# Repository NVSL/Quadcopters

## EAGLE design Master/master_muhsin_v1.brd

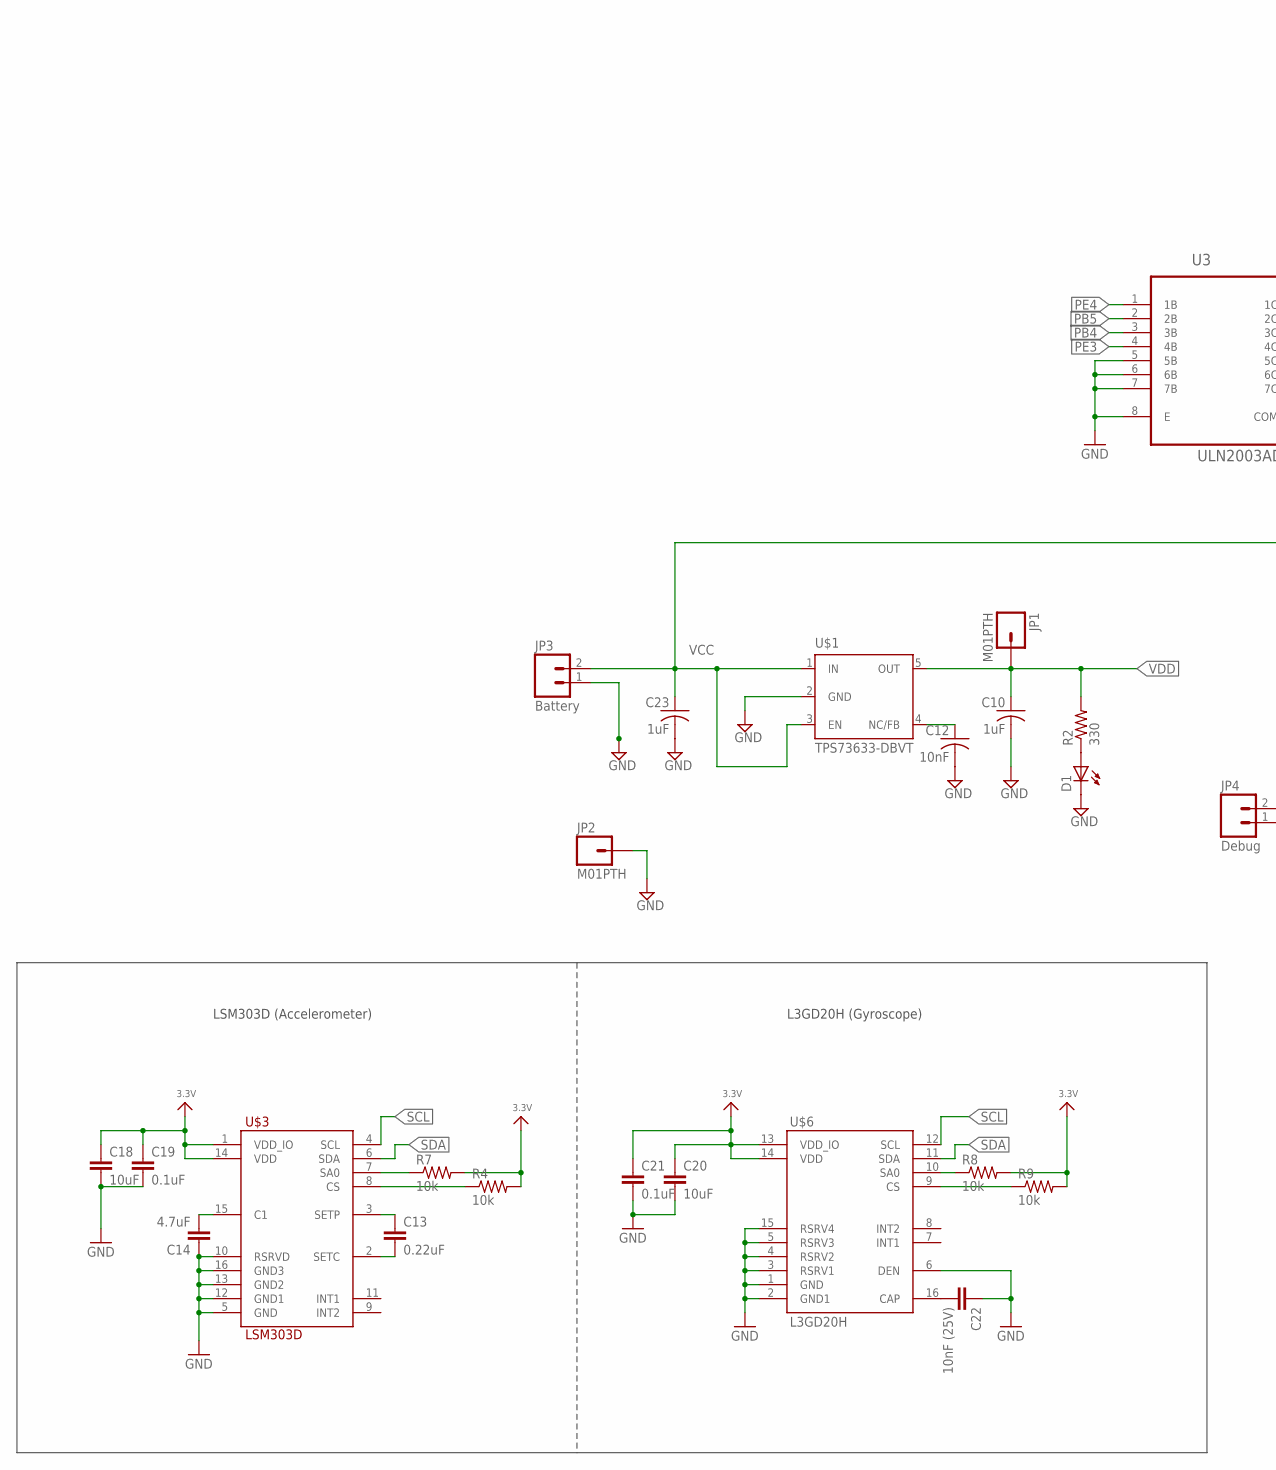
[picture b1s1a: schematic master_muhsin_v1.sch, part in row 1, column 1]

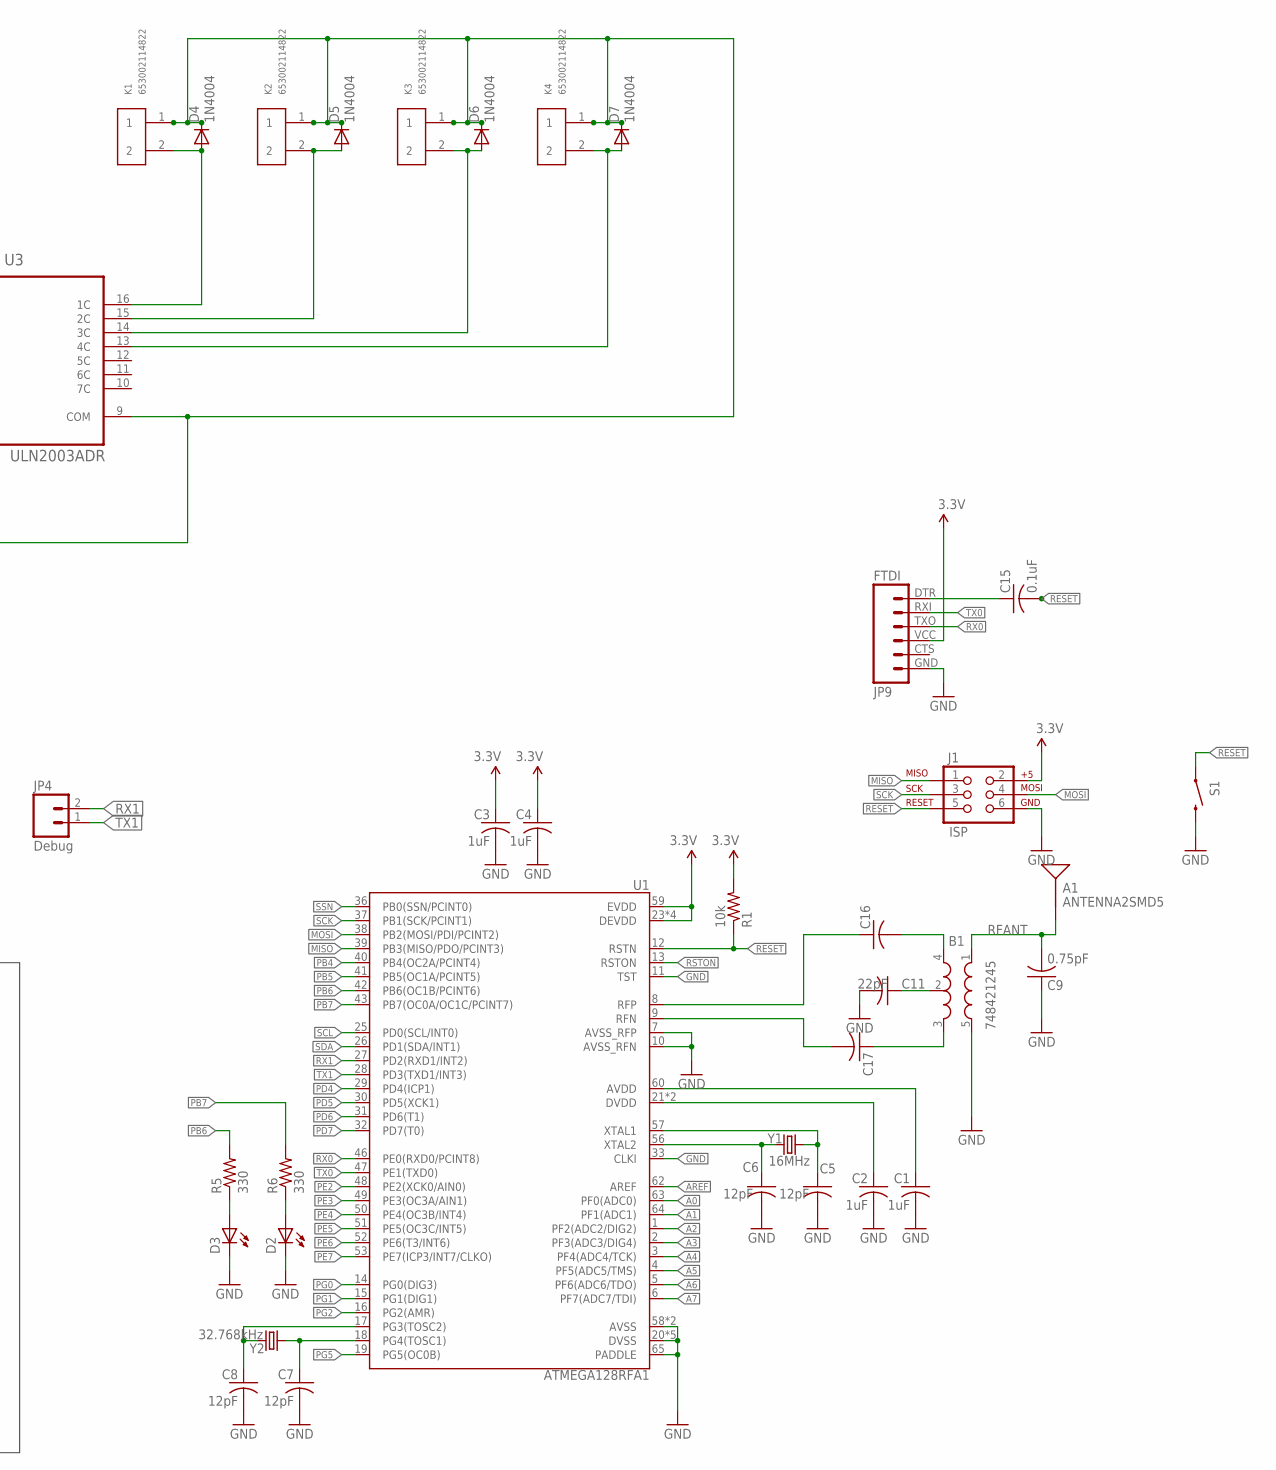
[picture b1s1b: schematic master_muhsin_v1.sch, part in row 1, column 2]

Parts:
A1: ANTENNA2SMD5; ANTENNA-CHIP5
B1: 748421245; BALUN
C1, C2, C3, C4, C10, C23: 1uF; C0805
C5, C6, C7, C8: 12pF; C0805
C9: 0.75pF; C0805
C11: 22pF; C0805
C12: 10nF; C0805
C13: 0.22uF; 0805
C14: 4.7uF; 0805
C15: 0.1uF; C0805
C16, C17: C-USC0805; C0805
C18, C20: 10uF; 0805
C19, C21: 0.1uF; 0805
C22: 10nF (25V); 0805
D1, D2, D3: LED5MM
D4, D5, D6, D7: 1N4004; DO41-10; MPN 1N4004
J1: ISP; 2X3-NS
JP1, JP2: M01PTH; 1X01
JP3: Battery; 1X02
JP4: Debug; 1X02
JP9: FTDI; FTDI_BASIC
K1, K2, K3, K4: 653002114822
R1: 10k; R0805
R2, R5, R6: 330; R0805
R4, R7, R8, R9: 10k; 0805
S1: SWITCH-MOMENTARY-2SMD; TACTILE_SWITCH_SMD
U1: ATMEGA128RFA1; QFN-64
U3: ULN2003ADR; SOIC127P600X175-16N
U$1: TPS73633-DBVT; SOT23-DBV
U$3: LSM303D; LGA16_3X3MM
U$6: L3GD20H; LGA16_3X3MM
Y1: 16MHz; CRYSTAL-SMD-5X3
Y2: 32.768kHz; CRYSTAL-32KHZ-SMD

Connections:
3.3V: C3.1, C4.1, C18.1, C19.1, C20.1, C21.1, J1.2, JP9.VCC (4), R1.2, R4.2, R7.2, R8.2, R9.2, U1.23 (DEVDD), U1.34 (DEVDD), U1.44 (DEVDD), U1.54 (DEVDD), U1.59 (EVDD), U$3.1 (VDD_IO), U$3.14 (VDD), U$6.13 (VDD_IO), U$6.14 (VDD)
A0: U1.63 (PF0(ADC0))
A1: U1.64 (PF1(ADC1))
A2: U1.1 (PF2(ADC2/DIG2))
A3: U1.2 (PF3(ADC3/DIG4))
A4: U1.3 (PF4(ADC4/TCK))
A5: U1.4 (PF5(ADC5/TMS))
A6: U1.5 (PF6(ADC6/TDO))
A7: U1.6 (PF7(ADC7/TDI))
AREF: U1.62 (AREF)
AVDD: C1.1, U1.60 (AVDD)
DTR: C15.1, JP9.DTR (1)
DVDD: C2.1, U1.21 (DVDD), U1.22 (DVDD)
GND: B1.5 (GND), C1.2, C2.2, C3.2, C4.2, C5.2, C6.2, C7.2, C8.2, C9.1, C10.2, C11.2, C12.2, C14.1, C18.2, C19.2, C20.2, C21.2, C22.1, C23.2, D1.K (C), D2.K (C), D3.K (C), J1.6, JP2.1, JP3.1, JP9.GND (6), S1.3 (2), U1.7 (AVSS_RFP), U1.10 (AVSS_RFN), U1.11 (TST), U1.20 (DVSS), U1.24 (DVSS), U1.33 (CLKI), U1.35 (DVSS), U1.45 (DVSS), U1.55 (DVSS), U1.58 (AVSS), U1.61 (AVSS), U1.65 (PADDLE), U3.5 (5B), U3.6 (6B), U3.7 (7B), U3.8 (E), U$1.2 (GND), U$3.5 (GND), U$3.10 (RSRVD), U$3.12 (GND1), U$3.13 (GND2), U$3.16 (GND3), U$6.1 (GND), U$6.2 (GND1), U$6.3 (RSRV1), U$6.4 (RSRV2), U$6.5 (RSRV3), U$6.6 (DEN), U$6.15 (RSRV4)
MISO: J1.1, U1.39 (PB3(MISO/PDO/PCINT3))
MOSI: J1.4, U1.38 (PB2(MOSI/PDI/PCINT2))
unnamed: C12.1, U$1.4 (NC/FB)
unnamed: D1.A, R2.1
unnamed: C5.1, U1.57 (XTAL1), Y1.3 (2)
unnamed: C6.1, U1.56 (XTAL2), Y1.1
unnamed: C7.1, U1.18 (PG4(TOSC1)), Y2.X1 (1)
unnamed: C8.1, U1.17 (PG3(TOSC2)), Y2.X2 (2)
unnamed: B1.2 (GND), C11.1
unnamed: D3.A, R5.1
unnamed: C13.1, U$3.3 (SETP)
unnamed: B1.4 (OUT1), C16.2
unnamed: B1.3 (OUT2), C17.1
unnamed: C13.2, U$3.2 (SETC)
unnamed: D2.A, R6.1
unnamed: R4.1, U$3.8 (CS)
unnamed: R7.1, U$3.7 (SA0)
unnamed: C14.2, U$3.15 (C1)
unnamed: R8.1, U$6.10 (SA0)
unnamed: R9.1, U$6.9 (CS)
unnamed: C22.2, U$6.16 (CAP)
unnamed: D4.A, K1.2, U3.16 (1C)
unnamed: D5.A, K2.2, U3.15 (2C)
unnamed: D6.A, K3.2, U3.14 (3C)
unnamed: D7.A, K4.2, U3.13 (4C)
PB4: U1.40 (PB4(OC2A/PCINT4)), U3.3 (3B)
PB5: U1.41 (PB5(OC1A/PCINT5)), U3.2 (2B)
PB6: R5.2, U1.42 (PB6(OC1B/PCINT6))
PB7: R6.2, U1.43 (PB7(OC0A/OC1C/PCINT7))
PD4: U1.29 (PD4(ICP1))
PD5: U1.30 (PD5(XCK1))
PD6: U1.31 (PD6(T1))
PD7: U1.32 (PD7(T0))
PE2: U1.48 (PE2(XCK0/AIN0))
PE3: U1.49 (PE3(OC3A/AIN1)), U3.4 (4B)
PE4: U1.50 (PE4(OC3B/INT4)), U3.1 (1B)
PE5: U1.51 (PE5(OC3C/INT5))
PE6: U1.52 (PE6(T3/INT6))
PE7: U1.53 (PE7(ICP3/INT7/CLKO))
PG0: U1.14 (PG0(DIG3))
PG1: U1.15 (PG1(DIG1))
PG2: U1.16 (PG2(AMR))
PG5: U1.19 (PG5(OC0B))
RESET: C15.2, J1.5, R1.1, S1.1, U1.12 (RSTN)
RFANT: A1.FEED, B1.1 (IN), C9.2
RFN: C17.2, U1.9 (RFN)
RFP: C16.1, U1.8 (RFP)
RSTON: U1.13 (RSTON)
RX0: JP9.TXO (3), U1.46 (PE0(RXD0/PCINT8))
RX1: JP4.2, U1.27 (PD2(RXD1/INT2))
SCK: J1.3, U1.37 (PB1(SCK/PCINT1))
SCL: U1.25 (PD0(SCL/INT0)), U$3.4 (SCL), U$6.12 (SCL)
SDA: U1.26 (PD1(SDA/INT1)), U$3.6 (SDA), U$6.11 (SDA)
SSN: U1.36 (PB0(SSN/PCINT0))
TX0: JP9.RXI (2), U1.47 (PE1(TXD0))
TX1: JP4.1, U1.28 (PD3(TXD1/INT3))
VCC: C23.1, D4.C, D5.C, D6.C, D7.C, JP3.2, K1.1, K2.1, K3.1, K4.1, U3.9 (COM), U$1.1 (IN), U$1.3 (EN)
VDD: C10.1, JP1.1, R2.2, U$1.5 (OUT)

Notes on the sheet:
LSM303D (Accelerometer)
L3GD20H (Gyroscope)

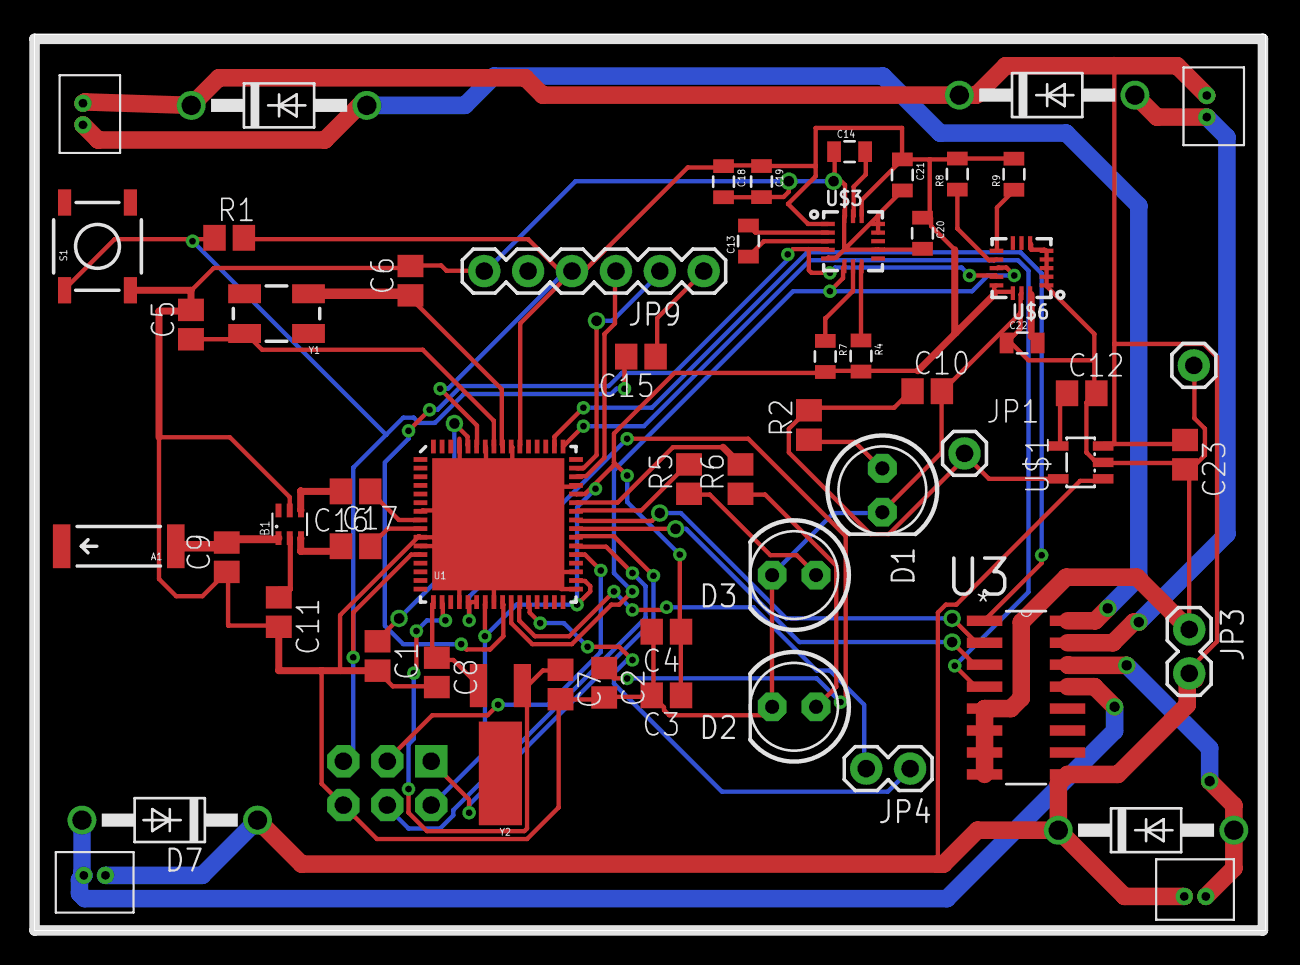
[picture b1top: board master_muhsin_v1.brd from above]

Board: 2 copper layers, 71.2 x 51.8 mm, 58 parts (0 on the bottom side), 49 nets.

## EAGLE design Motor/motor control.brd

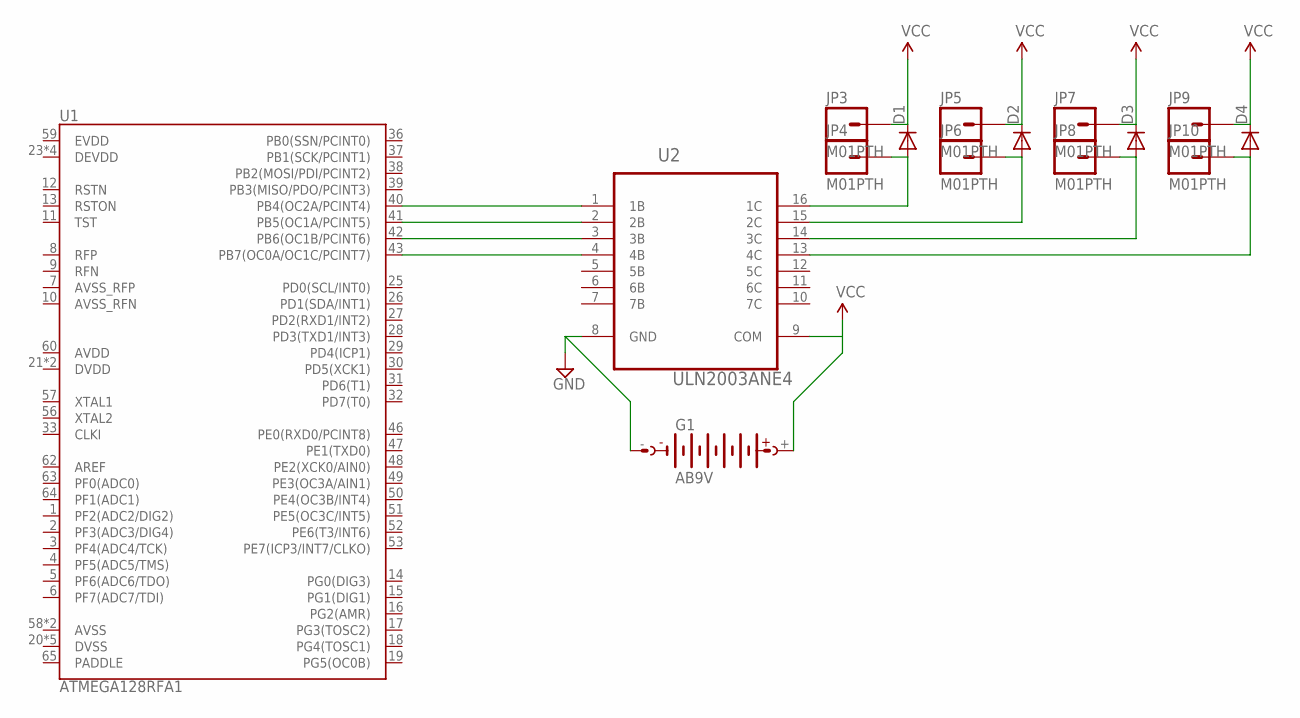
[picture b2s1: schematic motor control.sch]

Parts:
D1, D2, D3, D4: DIODE-D-5; D-5
G1: AB9V
JP3, JP4, JP5, JP6, JP7, JP8, JP9, JP10: M01PTH; 1X01
U1: ATMEGA128RFA1; QFN-64
U2: ULN2003ANE4; DIP254P762X508-16

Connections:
GND: G1.-, U2.8 (GND)
unnamed: U1.40 (PB4(OC2A/PCINT4)), U2.1 (1B)
unnamed: U1.41 (PB5(OC1A/PCINT5)), U2.2 (2B)
unnamed: U1.42 (PB6(OC1B/PCINT6)), U2.3 (3B)
unnamed: U1.43 (PB7(OC0A/OC1C/PCINT7)), U2.4 (4B)
unnamed: D1.A, JP4.1, U2.16 (1C)
unnamed: D4.A, JP10.1, U2.13 (4C)
unnamed: D3.A, JP8.1, U2.14 (3C)
unnamed: D2.A, JP6.1, U2.15 (2C)
VCC: D1.C, D2.C, D3.C, D4.C, G1.+, JP3.1, JP5.1, JP7.1, JP9.1, U2.9 (COM)

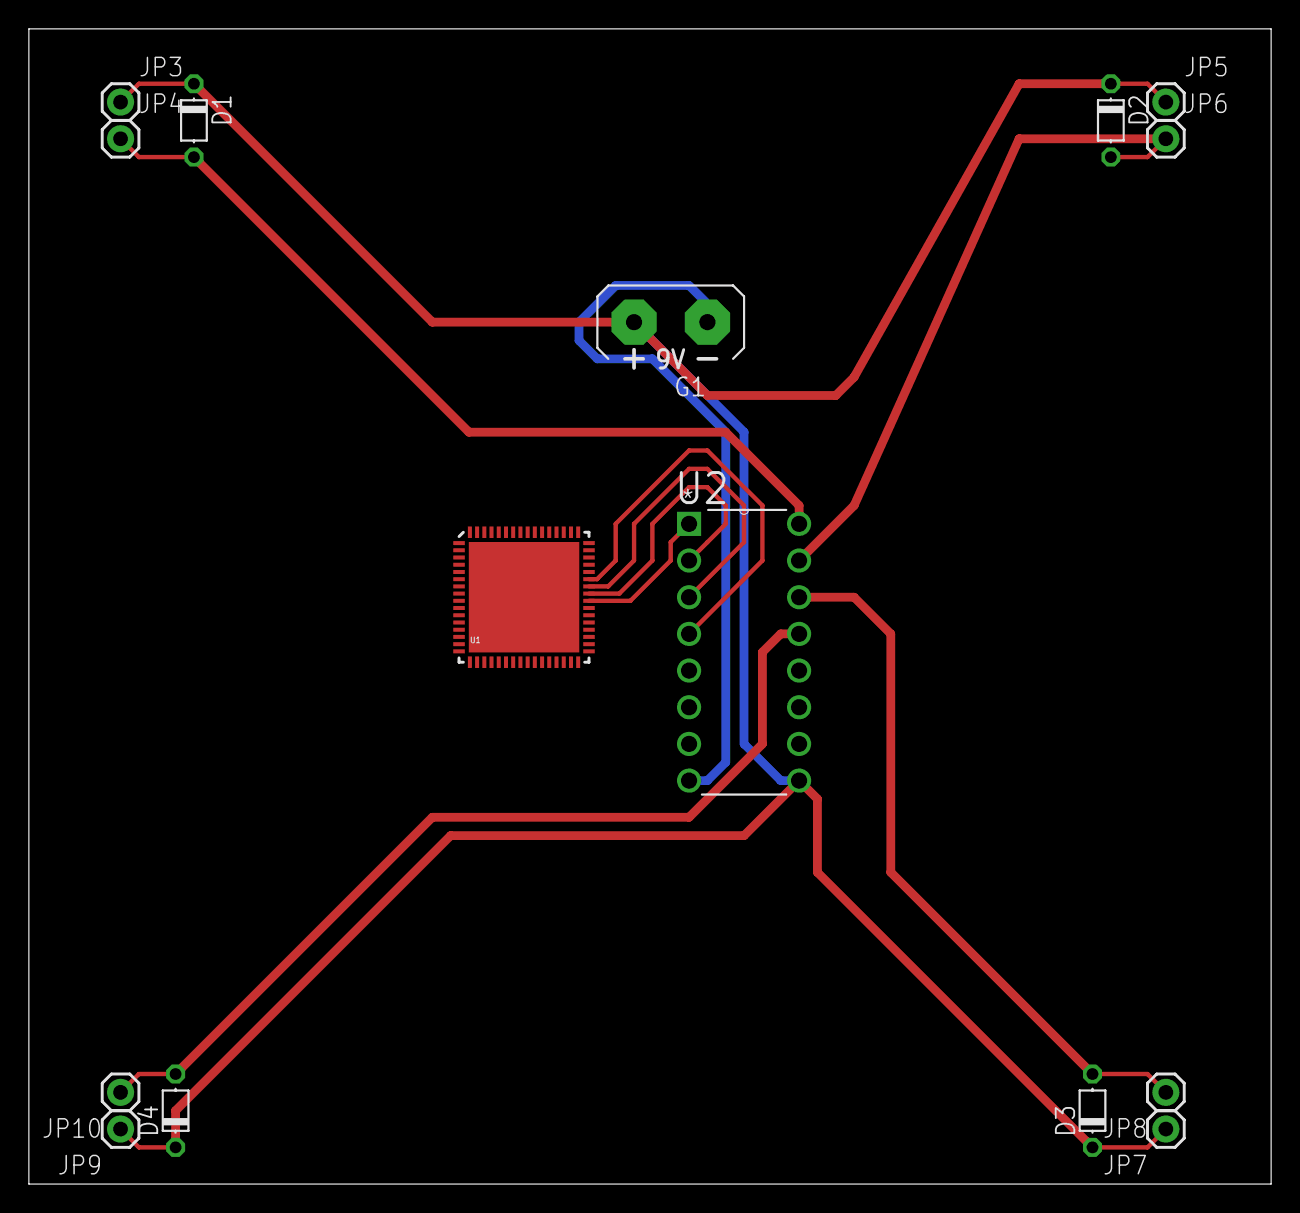
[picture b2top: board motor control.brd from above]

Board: 2 copper layers, 86.0 x 80.0 mm, 15 parts (0 on the bottom side), 10 nets.

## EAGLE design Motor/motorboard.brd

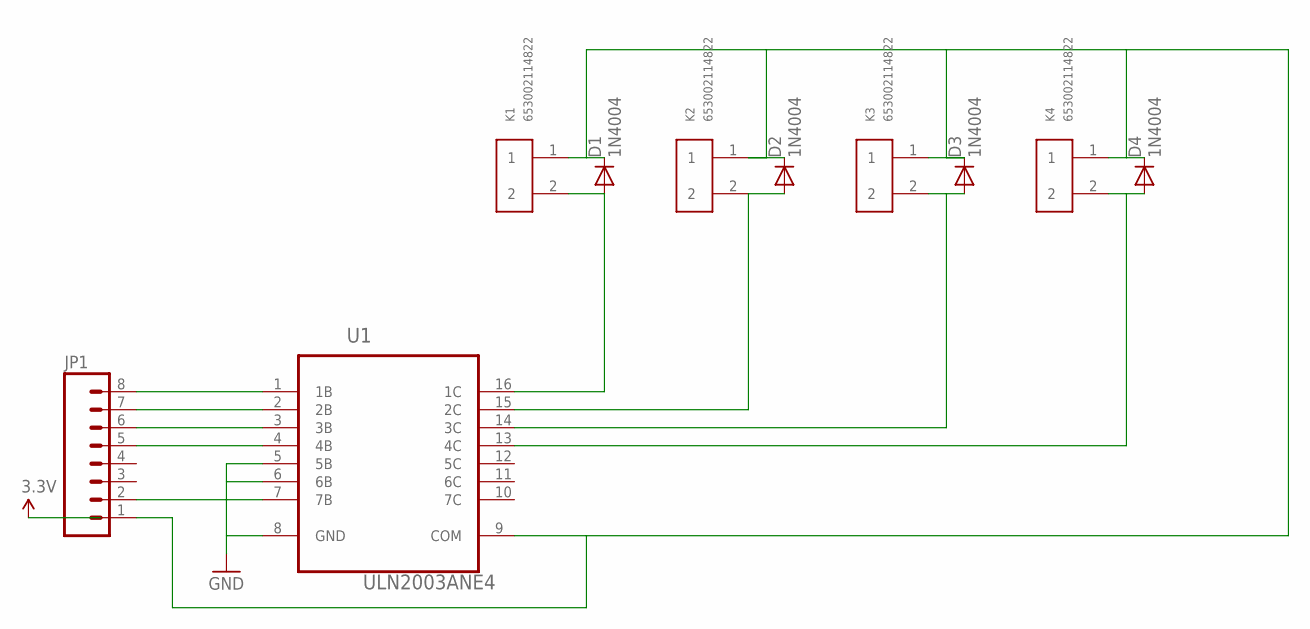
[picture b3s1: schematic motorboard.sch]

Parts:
D1, D2, D3, D4: 1N4004; DO41-10; MPN 1N4004
JP1: M08NO_SILK_FEMALE_PTH; 1X08_NO_SILK
K1, K2, K3, K4: 653002114822
U1: ULN2003ANE4; DIP254P762X508-16

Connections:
GND: JP1.2, U1.5 (5B), U1.6 (6B), U1.7 (7B), U1.8 (GND)
unnamed: D1.C, D2.C, D3.C, D4.C, JP1.1, K1.1, K2.1, K3.1, K4.1, U1.9 (COM)
unnamed: JP1.8, U1.1 (1B)
unnamed: JP1.7, U1.2 (2B)
unnamed: JP1.6, U1.3 (3B)
unnamed: JP1.5, U1.4 (4B)
unnamed: D1.A, K1.2, U1.16 (1C)
unnamed: D2.A, K2.2, U1.15 (2C)
unnamed: D3.A, K3.2, U1.14 (3C)
unnamed: D4.A, K4.2, U1.13 (4C)

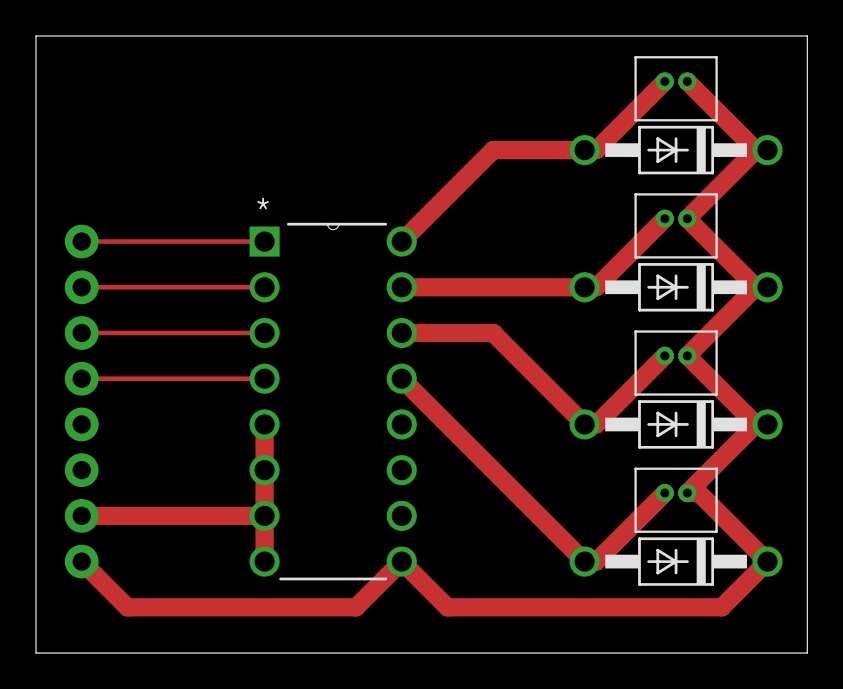
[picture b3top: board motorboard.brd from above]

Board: 2 copper layers, 42.9 x 34.3 mm, 10 parts (0 on the bottom side), 10 nets.

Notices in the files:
parts and their libraries:
SparkFun-RF: Licensing: CC v3.0 Share-Alike You are welcome to use this library for commercial purposes.
SparkFun-Capacitors: Licensing: Creative Commons ShareAlike 4.0 International - https://creativecommons.org/licenses/by-sa/4.0
